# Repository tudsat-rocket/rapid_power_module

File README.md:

# Frodo Power Module

The battery boards for the FRoDO-rockets

## Version 1

@todo

## Version 2

The newest version of the battery developed for the FRoDO-M-rocket 

The battery module contains two lithium-ion cells in series, mounted on an *SRAD* *PCB* using a Keystone connector, allowing the replacement of battery cells. 

The battery features a linear charging IC supporting up to 700 mA of charge current and performs balancing of the cells, powered by the charge bus through a reverse current protection diode and a PTC fuse.

### Components

- 2x 3000 mA h Sony VTC6 18650 lithium-ion cells in series
- for other components see https://github.com/tudsat-rocket/frodo_power_module/blob/main/frodo_power_module.csv

### Usage

| Connector   | Purpose                                             |
| ----------- | --------------------------------------------------- |
| FC          | connect the flight computer. Outputs 8v with max ?a |
| SW          | Switch to turn the battery board on and off         |
| FC-CAN (2x) | CAN-bus for communication                           |
| BUS-A       |                                                     |
| BUS-B       |                                                     |

Spanning liegt von außen an, geht durch Arming Circuit,

## Version 3

tdb...

### ToDos for Hyacinth

- 3x 18650 lithium-ion cells in series

- New Charging IC due to more Cells

- Larger Board due to more Cells.

- Are 18650 a requirement or might they be exchanged against softbody batteries known from drones? (smaller PCB possible)

- Arming Schalter schaltet alles an.

- 

- 6 Pin durch 8 Pin ersetzen
  
  #### Possible new ICs

- https://www.ti.com/lit/ds/symlink/bq25820.pdf?ts=1739830650898&ref_url=https%253A%252F%252Fwww.ti.com%252Fbattery-management%252Fcharger-ics%252Fproducts.html

#### Ideas for Cell Voltage balancing

Good:
bq76PL536A: https://www.ti.com/lit/ds/symlink/bq76pl536a.pdf?ts=1740396899518&ref_url=https%253A%252F%252Fwww.ti.com%252Fproduct%252FBQ76PL536A - Does not require host, is availabel on lcsc: https://www.lcsc.com/search?q=BQ76PL536A&s_z=n_BQ76PL536A
BQ76922: https://www.ti.com/lit/ds/symlink/bq76922.pdf?ts=1740361016781

Okay:
BQ79606A-Q1: https://www.ti.com/lit/ds/symlink/bq79606a-q1.pdf?ts=1740391966301&ref_url=https%253A%252F%252Fwww.ti.com%252Fproduct%252FBQ79606A-Q1 - Availability is bad

Meh:
BQ76925: https://www.ti.com/lit/ds/symlink/bq76925.pdf?ts=1740385881236 - due to required host. This is just an analogue expander.

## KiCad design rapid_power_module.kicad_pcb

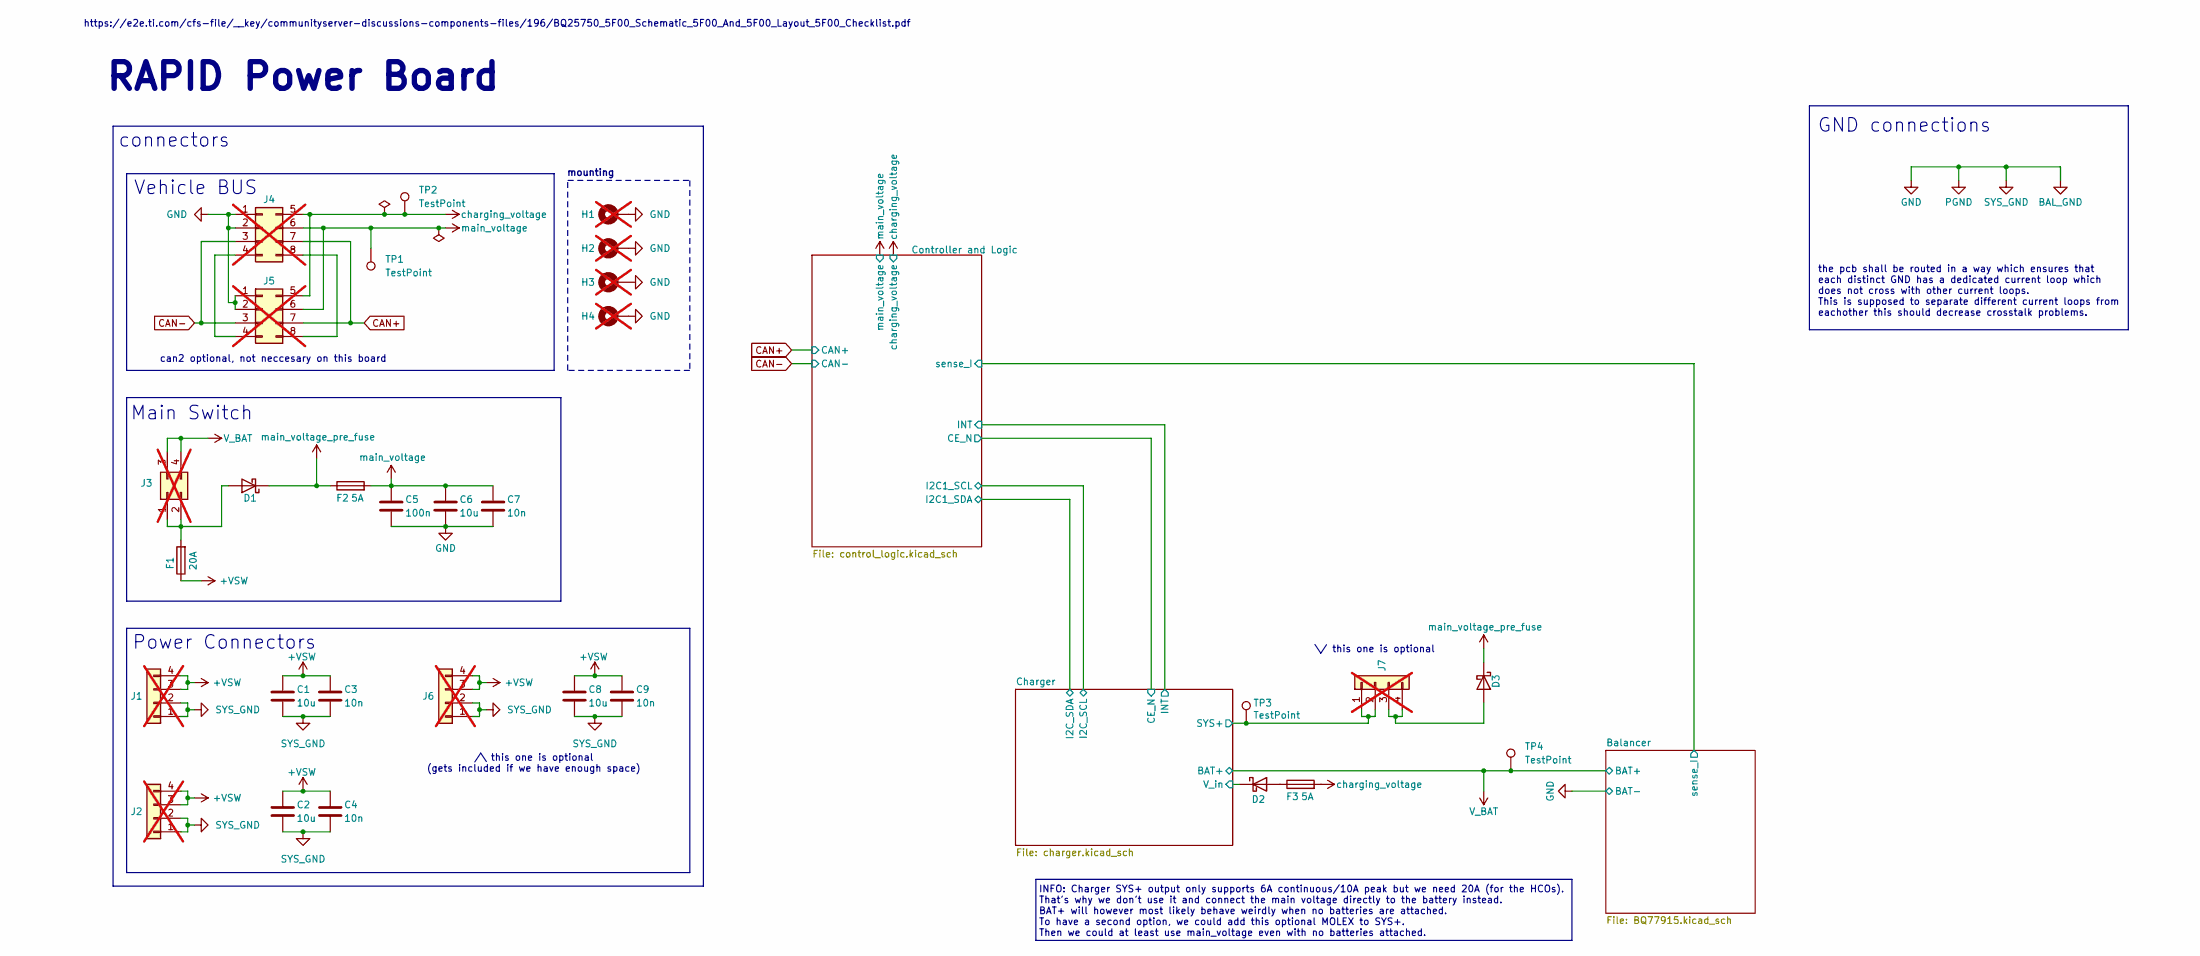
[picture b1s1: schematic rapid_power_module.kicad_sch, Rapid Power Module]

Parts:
C1, C2, C6, C8: 10u; C_0603_1608Metric; LCSC C96446
C3, C4, C7, C9: 10n; C_0402_1005Metric; LCSC C15195
C5: 100n; C_0402_1005Metric; LCSC C307331
D1, D2, D3: D_SMA; LCSC C22452
F1: 20A; Fuse_2010_5025Metric_Pad1.52x2.65mm_HandSolder; LCSC C2762483
F2, F3: 5A; Fuse_1206_3216Metric_Pad1.42x1.75mm_HandSolder; LCSC C48332
H1, H2, H3, H4: MountingHole_Pad; MountingHole_3.2mm_M3_Pad_Via; LCSC x; not fitted
J1, J2: Molex MicroFit 2x2; Molex_Micro-Fit_3.0_43045-0400_2x02_P3.00mm_Horizontal; Part# 0430450400; LCSC C122413; not fitted
J3: Molex MicroFit 2x2; Molex_Micro-Fit_3.0_43045-0400_2x02_P3.00mm_Horizontal; LCSC C122413; not fitted
J4, J5: Conn_02x04_Top_Bottom; Molex_Micro-Fit_3.0_43045-0800_2x04_P3.00mm_Horizontal; LCSC x; not fitted
J6, J7: Molex MicroFit 2x2; Molex_Micro-Fit_3.0_43045-0400_2x02_P3.00mm_Horizontal; Part# 0430450400; LCSC# C122413; not fitted
TP1, TP2, TP3, TP4: TestPoint; TestPoint_Pad_D2.0mm

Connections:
+VSW: C1.1, C2.1, C3.1, C4.1, C8.1, C9.1, F1.1, J1.3, J1.4, J2.3, J2.4, J6.3, J6.4
/Charger/SYS+: J7.1, J7.2, TP3.1 (1_1); also elsewhere on the board
/Charger/V_in: D2.1 (K); also elsewhere on the board
BAL_GND: C1.2, C2.2, C3.2, C4.2, C5.2, C6.2, C7.2, C8.2, C9.2, H1.1 (1_1), H2.1 (1_1), H3.1 (1_1), H4.1 (1_1), J1.1, J1.2, J2.1, J2.2, J4.1, J4.2, J5.1, J5.2, J6.1, J6.2; also elsewhere on the board
CAN+: J4.7, J5.7; also elsewhere on the board
CAN-: J4.3, J5.3; also elsewhere on the board
unnamed: D1.2 (A), F1.2, J3.1, J3.2
unnamed: D2.2 (A), F3.1
unnamed: D3.2 (A), J7.3, J7.4
unnamed: J4.4, J5.4
unnamed: J4.8, J5.8
V_BAT: J3.3, J3.4, TP4.1 (1_1); also elsewhere on the board
charging_voltage: F3.2, J4.5, J5.5, TP2.1 (1_1); also elsewhere on the board
main_voltage: C5.1, C6.1, C7.1, F2.2, J4.6, J5.6, TP1.1 (1_1); also elsewhere on the board
main_voltage_pre_fuse: D1.1 (K), D3.1 (K), F2.1

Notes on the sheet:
the pcb shall be routed in a way which ensures that each distinct GND has a dedicated current loop which does not cross with other current loops. This is supposed to separate different current loops from eachother this should decrease crosstalk problems.
connectors
can2 optional, not neccesary on this board
Vehicle BUS
Main Switch
RAPID Power Board
https://e2e.ti.com/cfs-file/__key/communityserver-discussions-components-files/196/BQ25750_5F00_Schematic_5F00_And_5F00_Layout_5F00_Checklist.pdf
\/ this one is optional
INFO: Charger SYS+ output only supports 6A continuous/10A peak but we need 20A (for the HCOs). That's why we don't use it and connect the main voltage directly to the battery instead. BAT+ will however most likely behave weirdly when no batteries are attached. To have a second option, we could add 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
mounting
/\ this one is optional (gets included if we have enough space)
Power Connectors
GND connections

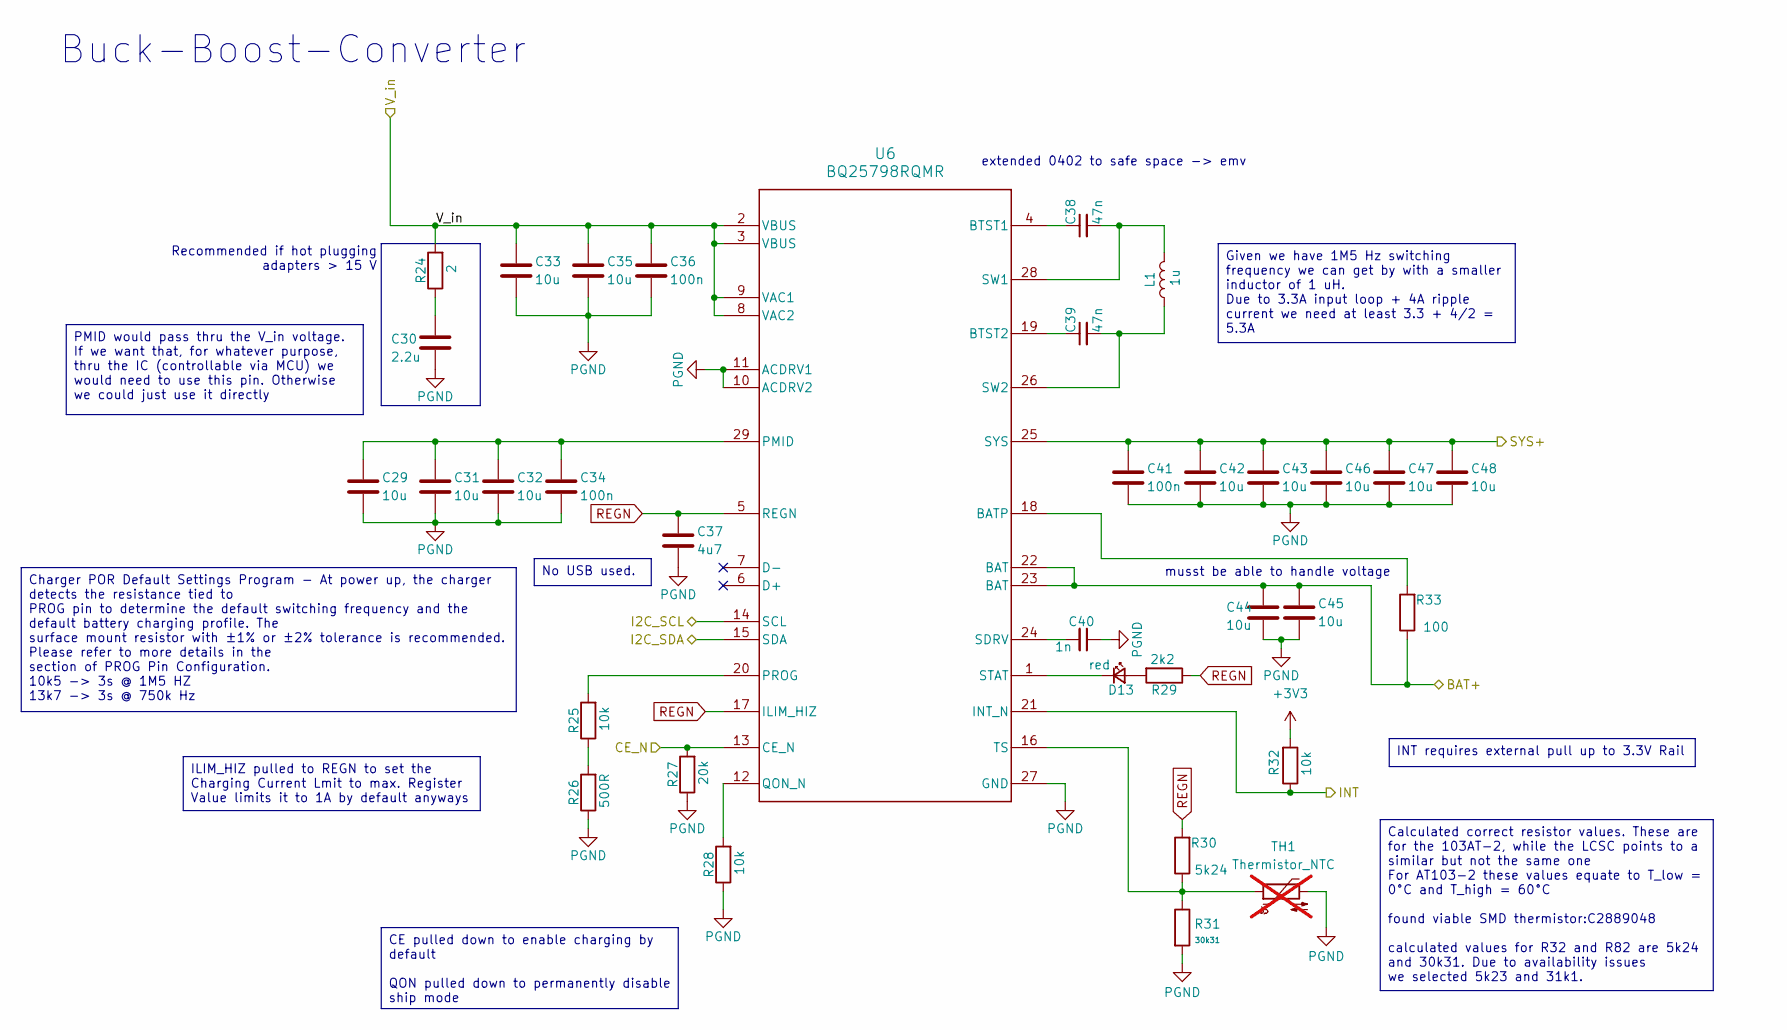
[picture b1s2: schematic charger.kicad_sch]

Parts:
C29, C31, C32, C33, C35, C42, C43, C44, C45, C46, C47, C48: 10u; C_0603_1608Metric; LCSC C96446
C30: 2.2u; C_0805_2012Metric; LCSC C377773
C34, C36, C41: 100n; C_0402_1005Metric; LCSC C307331
C37: 4u7; C_0402_1005Metric; LCSC C23733
C38, C39: 47n; C_0402_1005Metric; LCSC C82219
C40: 1n; C_0402_1005Metric; LCSC C1523
D13: red; LED_0603_1608Metric; LCSC C2286
L1: 1u; L_Wurth_WE-LQSH-3012; LCSC C7423316
R24: 2; R_0603_1608Metric; LCSC C22977
R25, R28, R32: 10k; R_0402_1005Metric; LCSC C25744
R26: 500R; R_0402_1005Metric; LCSC C25123
R27: 20k; R_0603_1608Metric; LCSC C4184
R29: 2k2; R_0402_1005Metric; LCSC C25879
R30: 5k24; R_0603_1608Metric; LCSC C23068
R31: 30k31; R_0805_2012Metric; LCSC C21841
R33: 100; R_0402_1005Metric; LCSC C25076
TH1: Thermistor_NTC; R_0603_1608Metric_Pad0.98x0.95mm_HandSolder; LCSC C2889048; not fitted
U6: BQ25798RQMR; IC_BQ25798RQMR; LCSC C2876593

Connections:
+3V3: R32.2; also elsewhere on the board
/Charger/CE_N: R27.2, U6.13 (CE_N); also elsewhere on the board
/Charger/INT: R32.1, U6.21 (INT_N); also elsewhere on the board
/Charger/SYS+: C41.1, C42.1, C43.1, C46.1, C47.1, C48.1, U6.25 (SYS); also elsewhere on the board
/Charger/V_in: C33.1, C35.1, C36.1, R24.2, U6.2 (VBUS), U6.3 (VBUS), U6.8 (VAC2), U6.9 (VAC1); also elsewhere on the board
BAL_GND: C29.2, C30.2, C31.2, C32.2, C33.2, C34.2, C35.2, C36.2, C37.2, C40.1, C41.2, C42.2, C43.2, C44.2, C45.2, C46.2, C47.2, C48.2, R26.1, R27.1, R28.1, R31.2, TH1.2, U6.10 (ACDRV2), U6.11 (ACDRV1), U6.27 (GND); also elsewhere on the board
I2C1_SCL: U6.14 (SCL); also elsewhere on the board
I2C1_SDA: U6.15 (SDA); also elsewhere on the board
unnamed: C30.1, R24.1
unnamed: D13.2 (A), R29.2
unnamed: D13.1 (K), U6.1 (STAT)
unnamed: R25.1, R26.2
unnamed: R33.2, U6.18 (BATP)
unnamed: C38.1, U6.4 (BTST1)
unnamed: C39.1, U6.19 (BTST2)
unnamed: C29.1, C31.1, C32.1, C34.1, U6.29 (PMID)
unnamed: R25.2, U6.20 (PROG)
unnamed: R28.2, U6.12 (QON_N)
unnamed: C40.2, U6.24 (SDRV)
unnamed: C38.2, L1.2, U6.28 (SW1)
unnamed: C39.2, L1.1, U6.26 (SW2)
unnamed: R30.1, R31.1, TH1.1, U6.16 (TS)
REGN: C37.1, R29.1, R30.2, U6.5 (REGN), U6.17 (ILIM_HIZ)
V_BAT: C44.1, C45.1, R33.1, U6.22 (BAT), U6.23 (BAT); also elsewhere on the board

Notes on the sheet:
extended 0402 to safe space -> emv
Buck-Boost-Converter
Recommended if hot plugging adapters > 15 V
musst be able to handle voltage
ILIM_HIZ pulled to REGN to set the Charging Current Lmit to max. Register Value limits it to 1A by default anyways
Given we have 1M5 Hz switching frequency we can get by with a smaller inductor of 1 uH. Due to 3.3A input loop + 4A ripple current we need at least 3.3 + 4/2 = 5.3A
INT requires external pull up to 3.3V Rail
Calculated correct resistor values. These are for the 103AT-2, while the LCSC points to a similar but not the same one For AT103-2 these values equate to T_low = 0°C and T_high = 60°C found viable SMD thermistor:C2889048 calculated values for R32 and R82 are 5k24 and 30k31. Due to availability issu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
PMID would pass thru the V_in voltage. If we want that, for whatever purpose, thru the IC (controllable via MCU) we would need to use this pin. Otherwise we could just use it directly
CE pulled down to enable charging by default QON pulled down to permanently disable ship mode
No USB used.
Charger POR Default Settings Program - At power up, the charger detects the resistance tied to PROG pin to determine the default switching frequency and the default battery charging profile. The surface mount resistor with ±1% or ±2% tolerance is recommended. Please refer to more details in the sec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

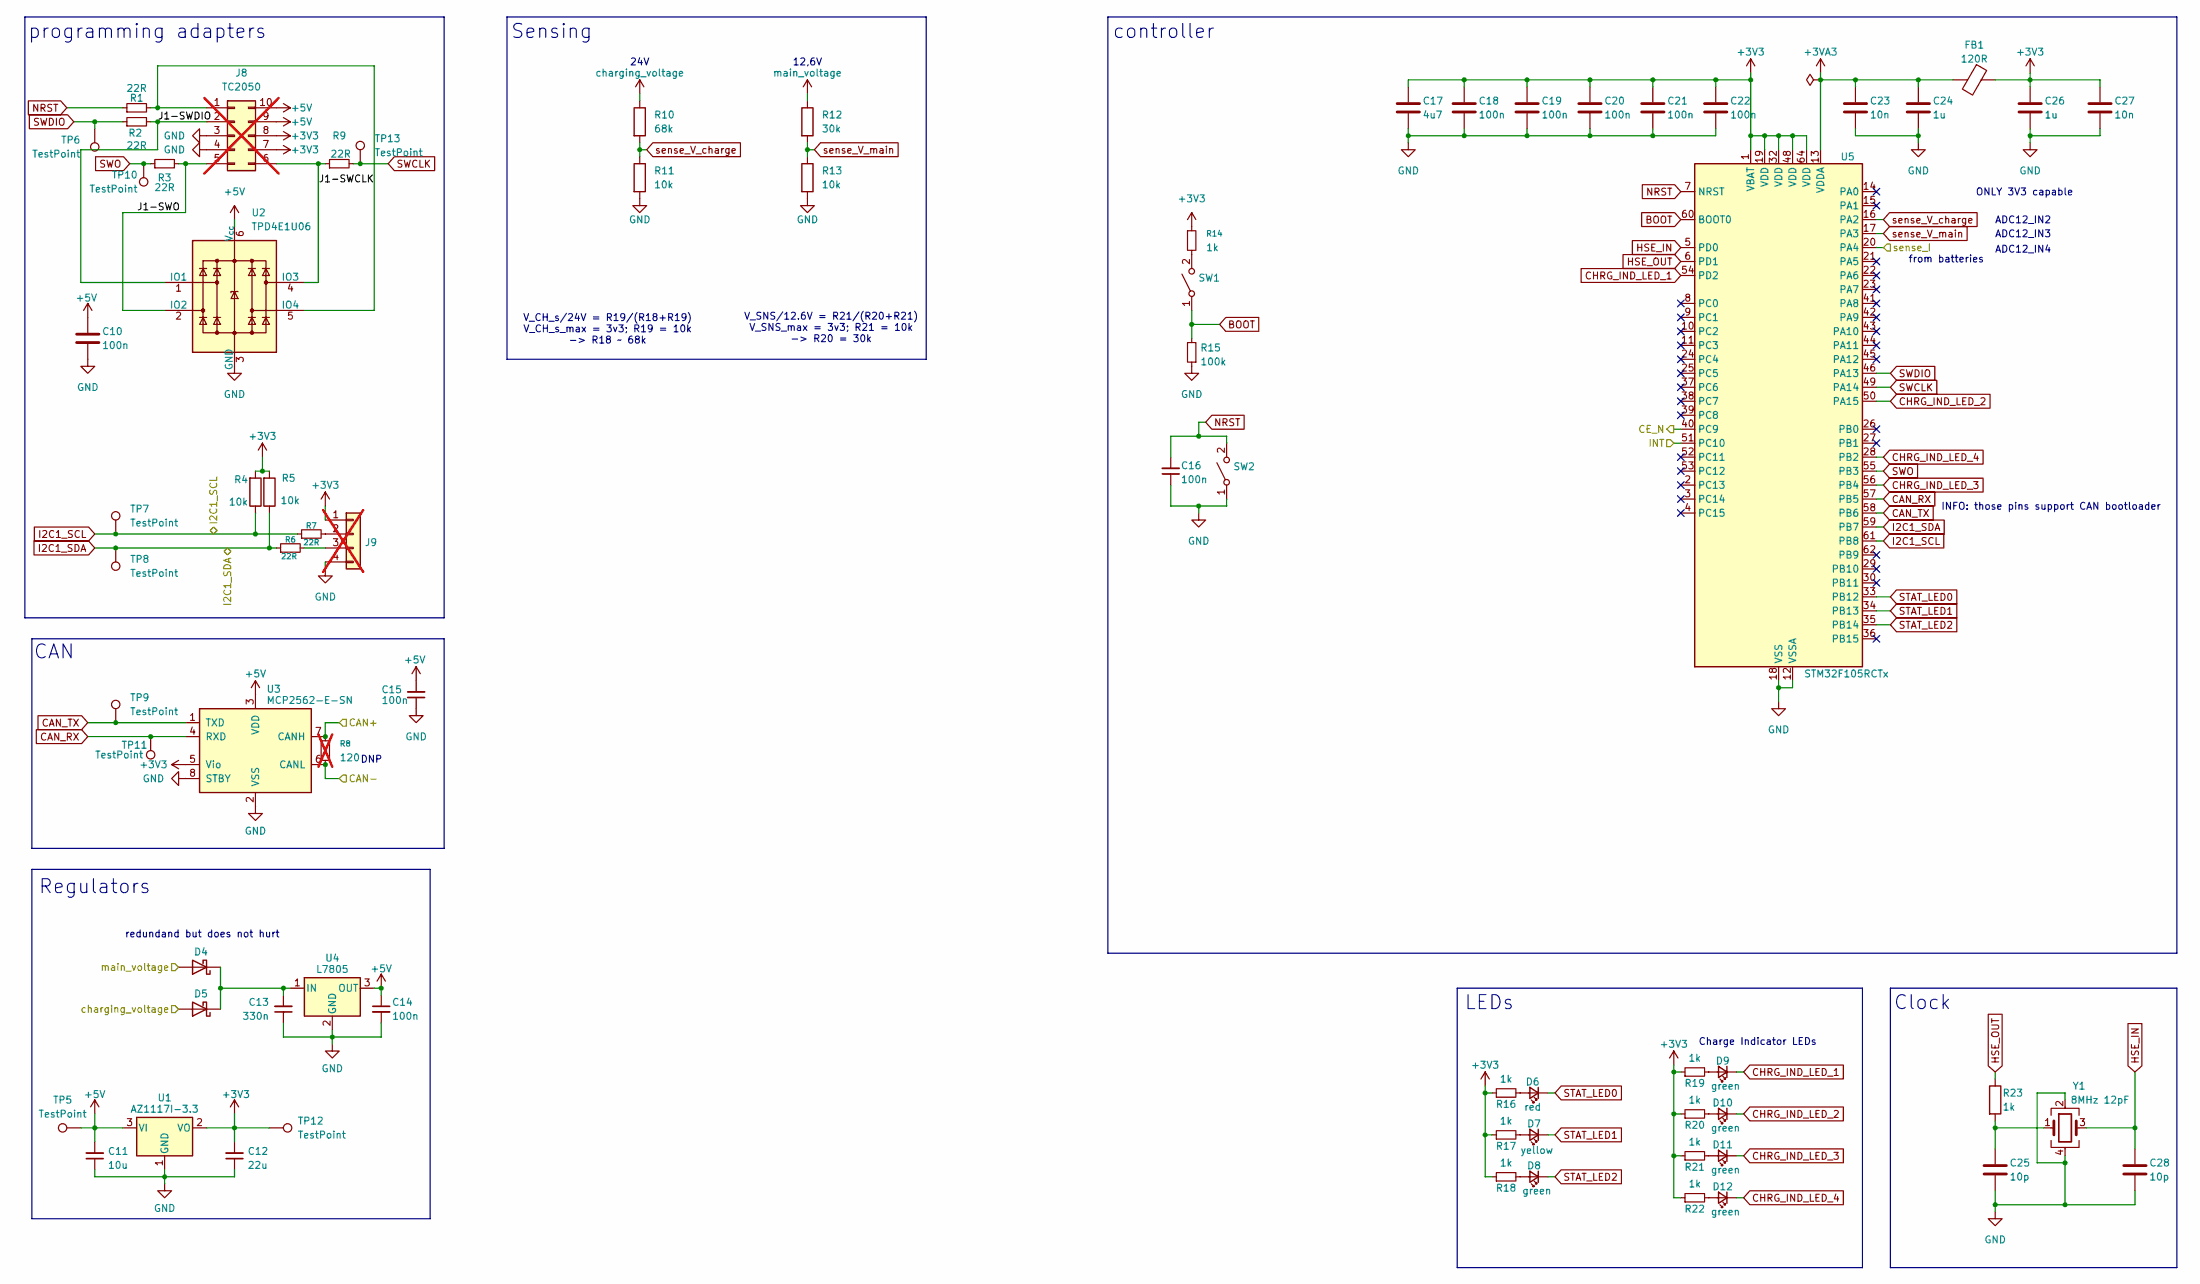
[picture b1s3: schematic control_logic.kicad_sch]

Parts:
C10, C15, C18, C19, C20, C21, C22: 100n; C_0402_1005Metric; LCSC C307331
C11: 10u; C_1206_3216Metric; Part# CL31A106KBHNNNE; LCSC C13585
C12: 22u; C_1206_3216Metric; Part# CL31A226KAHNNNE; LCSC C12891
C13: 330n; C_0603_1608Metric; Part# CL10B474KA8NNNC; LCSC C1615
C14: 100n; C_0402_1005Metric; Part# CC0603KRX7R9BB104; LCSC C307331
C16: 100n; C_0402_1005Metric; Part# CL10B104KB8NNNC; LCSC C307331
C17: 4u7; C_0402_1005Metric; LCSC C23733
C23, C27: 10n; C_0402_1005Metric; LCSC C15195
C24, C26: 1u; C_0402_1005Metric; LCSC C52923
C25, C28: 10p; C_0402_1005Metric; LCSC C32949
D4, D5: D_SMA; LCSC C22452
D6: red; LED_0603_1608Metric; LCSC C2286
D7: yellow; LED_0805_2012Metric; LCSC C2296
D8, D9, D10, D11, D12: green; LED_0805_2012Metric; LCSC C2297
FB1: 120R; L_0603_1608Metric; Part# BLM18PG121SN1D; LCSC C14709
J8: TC2050; Tag-Connect_TC2050-IDC-FP_2x05_P1.27mm_Vertical; LCSC x; not fitted
J9: SWD Header; PinHeader_1x04_P2.54mm_Vertical_SMD_Pin1Left; LCSC x; not fitted
R1, R2, R3, R9: 22R; R_0402_1005Metric; Part# RC0603FR-0710KL; LCSC C25092
R4, R5, R11, R13: 10k; R_0402_1005Metric; LCSC C25744
R6, R7: 22R; R_0402_1005Metric; Part# RC0603FR-0722RL; LCSC C25092
R8: 120; C_0402_1005Metric; LCSC C25079; not fitted
R10: 68k; R_0603_1608Metric; LCSC C23231
R12: 30k; R_0603_1608Metric; LCSC C22984
R14, R16, R17, R18, R19, R20, R21, R22, R23: 1k; R_0402_1005Metric; LCSC C11702
R15: 100k; R_0402_1005Metric; Part# RC0603FR-0710KL; LCSC C25741
SW1, SW2: SW_SPST_TS-1088-xR020; LCSC C720477
TP5, TP6, TP7, TP8, TP9, TP10, TP11, TP12, TP13: TestPoint; TestPoint_Pad_D2.0mm
U1: AZ1117I-3.3; SOT-223-3_TabPin2; Part# AZ1117CH-3.3TRG1; LCSC C92102
U2: TPD4E1U06; SOT-563; LCSC C527516
U3: MCP2562-E-SN; SOIC-8_3.9x4.9mm_P1.27mm; Part# MCP2562-H/SN; DigiKey# MCP2562-H/SN
U4: L7805; TO-252-2; Part# L78M05ABDT-TR; LCSC C58069
U5: STM32F105RCTx; LQFP-64_10x10mm_P0.5mm; LCSC C8345
Y1: 8MHz 12pF; Crystal_SMD_5032-4Pin_5.0x3.2mm; Part# 5TJ480000NYLBC; LCSC C2149245

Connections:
+3V3: C12.2, C17.1, C18.1, C19.1, C20.1, C21.1, C22.1, C26.1, C27.1, FB1.1, J8.7, J8.8, J9.1, R4.2, R5.2, R14.1, R16.1, R17.1, R18.1, R19.1, R20.1, R21.1, R22.1, TP12.1 (1_1), U1.2 (VO), U3.5 (Vio), U5.1 (VBAT), U5.19 (VDD), U5.32 (VDD), U5.48 (VDD), U5.64 (VDD); also elsewhere on the board
+3VA3: C23.1, C24.1, FB1.2, U5.13 (VDDA)
+5V: C10.1, C11.2, C14.1, C15.2, J8.9, J8.10, TP5.1 (1_1), U1.3 (VI), U2.6 (V_{cc}), U3.3 (VDD), U4.3 (OUT)
/Balancer/sense_I: U5.20 (PA4); also elsewhere on the board
/Charger/CE_N: U5.40 (PC9); also elsewhere on the board
/Charger/INT: U5.51 (PC10); also elsewhere on the board
/Controller and Logic/J1-SWCLK: J8.6, R9.1, U2.4 (IO3)
/Controller and Logic/J1-SWDIO: J8.2, R2.2, U2.1 (IO1)
/Controller and Logic/J1-SWO: J8.5, R3.2, U2.2 (IO2)
BAL_GND: C10.2, C11.1, C12.1, C13.1, C14.2, C15.1, C16.1, C17.2, C18.2, C19.2, C20.2, C21.2, C22.2, C23.2, C24.2, C25.2, C26.2, C27.2, C28.2, J8.3, J8.4, J9.4, R11.2, R13.2, R15.1, SW2.1 (A), U1.1 (GND), U2.3 (GND), U3.2 (VSS), U3.8 (STBY), U4.2 (GND), U5.12 (VSSA), U5.18 (VSS), U5.31 (VSS), U5.47 (VSS), U5.63 (VSS), Y1.2, Y1.4; also elsewhere on the board
BOOT: R15.2, SW1.1 (A), U5.60 (BOOT0)
CAN+: R8.1, U3.7 (CANH); also elsewhere on the board
CAN-: R8.2, U3.6 (CANL); also elsewhere on the board
CAN_RX: TP11.1 (1_1), U3.4 (RXD), U5.57 (PB5)
CAN_TX: TP9.1 (1_1), U3.1 (TXD), U5.58 (PB6)
CHRG_IND_LED_1: D9.1 (K), U5.54 (PD2)
CHRG_IND_LED_2: D10.1 (K), U5.50 (PA15)
CHRG_IND_LED_3: D11.1 (K), U5.56 (PB4)
CHRG_IND_LED_4: D12.1 (K), U5.28 (PB2)
HSE_IN: C28.1, U5.5 (PD0), Y1.3
HSE_OUT: R23.1, U5.6 (PD1)
I2C1_SCL: R4.1, R7.1, TP7.1 (1_1), U5.61 (PB8); also elsewhere on the board
I2C1_SDA: R5.1, R6.1, TP8.1 (1_1), U5.59 (PB7); also elsewhere on the board
NRST: C16.2, R1.1, SW2.2 (B), U5.7 (NRST)
unnamed: C25.1, R23.2, Y1.1
unnamed: C13.2, D4.1 (K), D5.1 (K), U4.1 (IN)
unnamed: D6.2 (A), R16.2
unnamed: D7.2 (A), R17.2
unnamed: D8.2 (A), R18.2
unnamed: D9.2 (A), R19.2
unnamed: D10.2 (A), R20.2
unnamed: D11.2 (A), R21.2
unnamed: D12.2 (A), R22.2
unnamed: J8.1, R1.2, U2.5 (IO4)
unnamed: J9.2, R7.2
unnamed: J9.3, R6.2
unnamed: R14.2, SW1.2 (B)
STAT_LED0: D6.1 (K), U5.33 (PB12)
STAT_LED1: D7.1 (K), U5.34 (PB13)
STAT_LED2: D8.1 (K), U5.35 (PB14)
SWCLK: R9.2, TP13.1 (1_1), U5.49 (PA14)
SWDIO: R2.1, TP6.1 (1_1), U5.46 (PA13)
SWO: R3.1, TP10.1 (1_1), U5.55 (PB3)
charging_voltage: D5.2 (A), R10.1; also elsewhere on the board
main_voltage: D4.2 (A), R12.1; also elsewhere on the board
sense_V_charge: R10.2, R11.1, U5.16 (PA2)
sense_V_main: R12.2, R13.1, U5.17 (PA3)

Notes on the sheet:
Clock
INFO: those pins support CAN bootloader
controller
from batteries
Sensing
Charge Indicator LEDs
Regulators
redundand but does not hurt
V_SNS/12.6V = R21/(R20+R21) V_SNS_max = 3v3; R21 = 10k -> R20 = 30k
LEDs
ADC12_IN3
ADC12_IN4
programming adapters
ONLY 3V3 capable
12,6V
ADC12_IN2
DNP
CAN
24V
V_CH_s/24V = R19/(R18+R19) V_CH_s_max = 3v3; R19 = 10k -> R18 ~ 68k

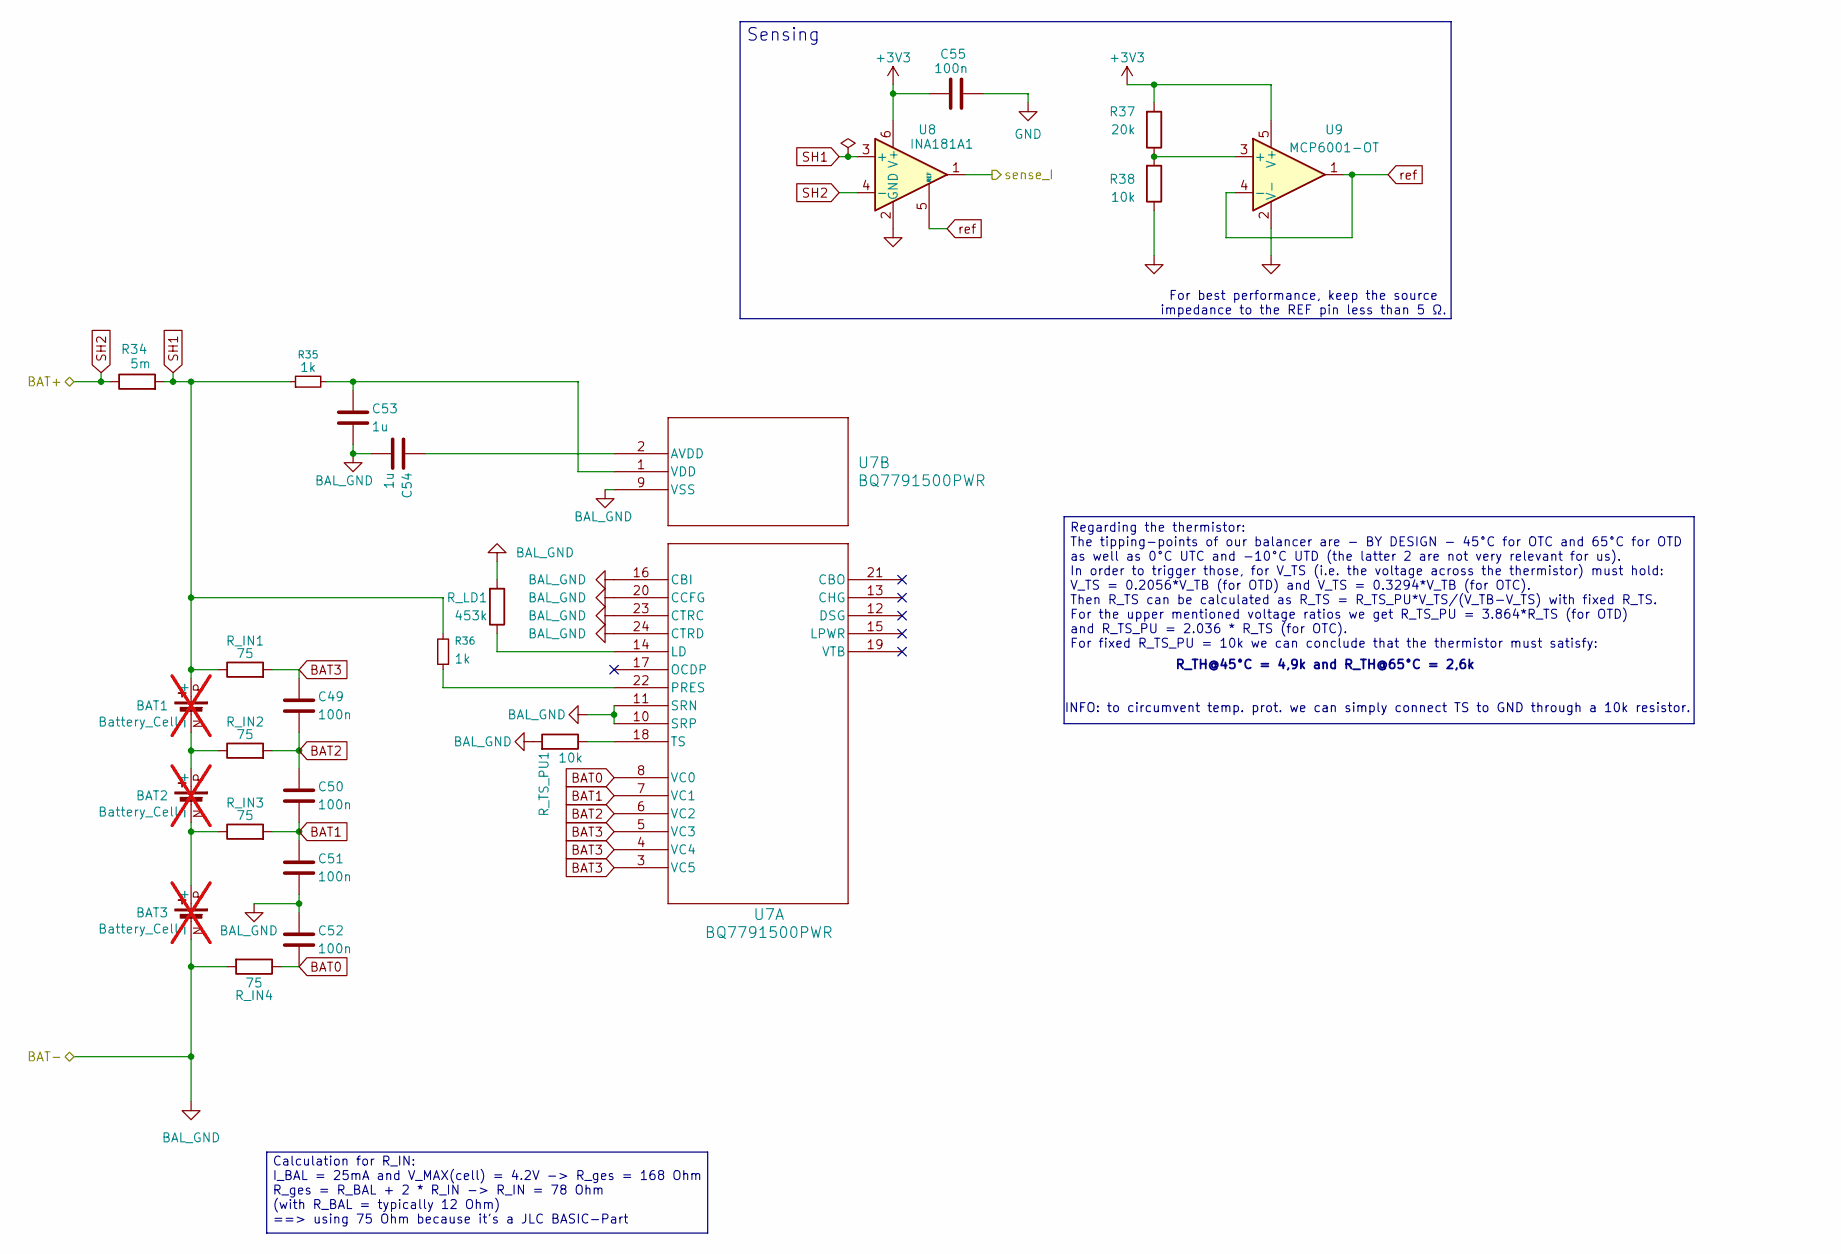
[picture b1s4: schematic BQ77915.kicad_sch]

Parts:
BAT1, BAT2, BAT3: Battery_Cell; BAT_1043; LCSC x; not fitted
C49, C50, C51, C52: 100n; C_0402_1005Metric; LCSC C307331
C53, C54: 1u; C_0402_1005Metric; LCSC C52923
C55: 100n; C_0402_1005Metric; LCSC C1525
R34: 5m; R_2512_6332Metric_Pad1.40x3.35mm_HandSolder; Part# DSLR-K-3-5F; LCSC C41382686
R35, R36: 1k; R_0402_1005Metric; LCSC C11702
R37: 20k; R_0402_1005Metric_Pad0.72x0.64mm_HandSolder; LCSC C25765
R38: 10k; R_0402_1005Metric_Pad0.72x0.64mm_HandSolder; LCSC C25744
R_IN1, R_IN2, R_IN3, R_IN4: 75; R_0603_1608Metric; LCSC C4275
R_LD1: 453k; R_0402_1005Metric; LCSC C27009
R_TS_PU1: 10k; R_0402_1005Metric; LCSC C25744
U7: BQ7791500PWR; TSSOP-24_4.4x7.8mm_P0.65mm; LCSC C2876946
U8: INA181A1; SOT-23-6; LCSC C2058943
U9: MCP6001-OT; SOT-23-5; LCSC C116490

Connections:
+3V3: C55.1, R37.2, U8.6 (V+), U9.5 (V+); also elsewhere on the board
/Balancer/sense_I: U8.1; also elsewhere on the board
BAL_GND: BAT3.N (-), C51.2, C52.1, C53.2, C54.2, C55.2, R38.1, R_IN4.2, R_LD1.2, R_TS_PU1.2, U7.9 (VSS), U7.10 (SRP), U7.11 (SRN), U7.16 (CBI), U7.20 (CCFG), U7.23 (CTRC), U7.24 (CTRD), U8.2 (GND), U9.2 (V-); also elsewhere on the board
BAT0: C52.2, R_IN4.1, U7.8 (VC0)
BAT1: C50.2, C51.1, R_IN3.2, U7.7 (VC1)
BAT2: C49.2, C50.1, R_IN2.2, U7.6 (VC2)
BAT3: C49.1, R_IN1.2, U7.3 (VC5), U7.4 (VC4), U7.5 (VC3)
unnamed: BAT1.N (-), BAT2.P (+), R_IN2.1
unnamed: BAT2.N (-), BAT3.P (+), R_IN3.1
unnamed: R_LD1.1, U7.14 (LD)
unnamed: R36.1, U7.22 (PRES)
unnamed: R_TS_PU1.1, U7.18 (TS)
unnamed: C54.1, U7.2 (AVDD)
unnamed: C53.1, R35.2, U7.1 (VDD)
unnamed: R37.1, R38.2, U9.3 (+)
SH1: BAT1.P (+), R34.2, R35.1, R36.2, R_IN1.1, U8.3 (+)
V_BAT: R34.1, U8.4 (-); also elsewhere on the board
ref: U8.5 (REF), U9.1, U9.4 (-)

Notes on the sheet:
For best performance, keep the source impedance to the REF pin less than 5 Ω.
R_TH@45°C = 4,9k and R_TH@65°C = 2,6k
INFO: to circumvent temp. prot. we can simply connect TS to GND through a 10k resistor.
Calculation for R_IN: I_BAL = 25mA and V_MAX(cell) = 4.2V -> R_ges = 168 Ohm R_ges = R_BAL + 2 * R_IN -> R_IN = 78 Ohm (with R_BAL = typically 12 Ohm) ==> using 75 Ohm because it's a JLC BASIC-Part
Regarding the thermistor: The tipping-points of our balancer are - BY DESIGN - 45°C for OTC and 65°C for OTD as well as 0°C UTC and -10°C UTD (the latter 2 are not very relevant for us). In order to trigger those, for V_TS (i.e. the voltage across the thermistor) must hold: V_TS = 0.2056*V_TB (for 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
Sensing

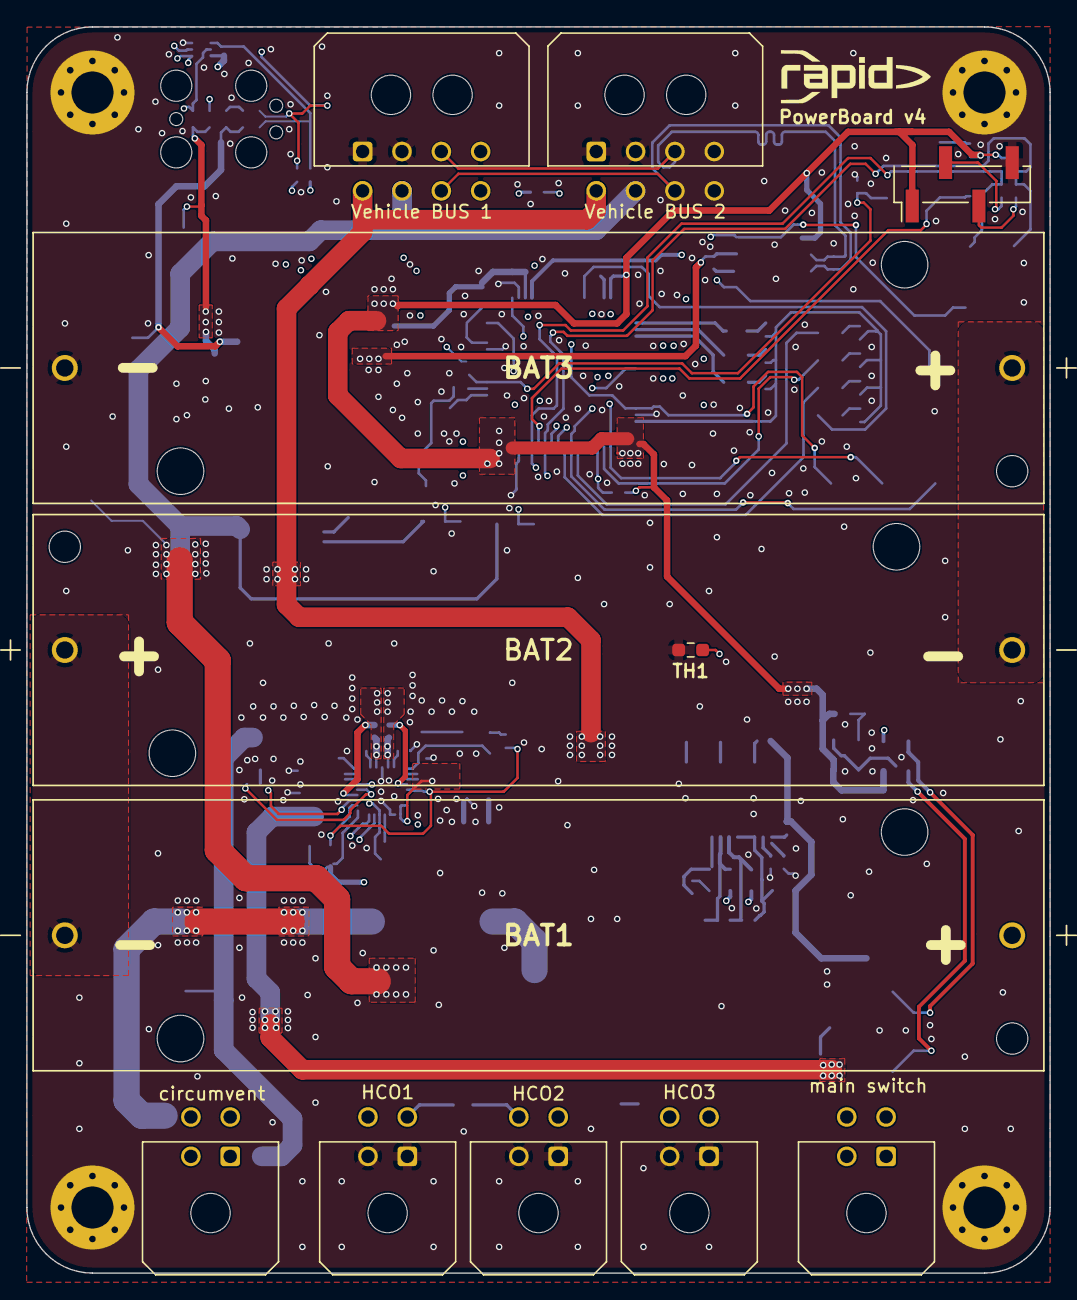
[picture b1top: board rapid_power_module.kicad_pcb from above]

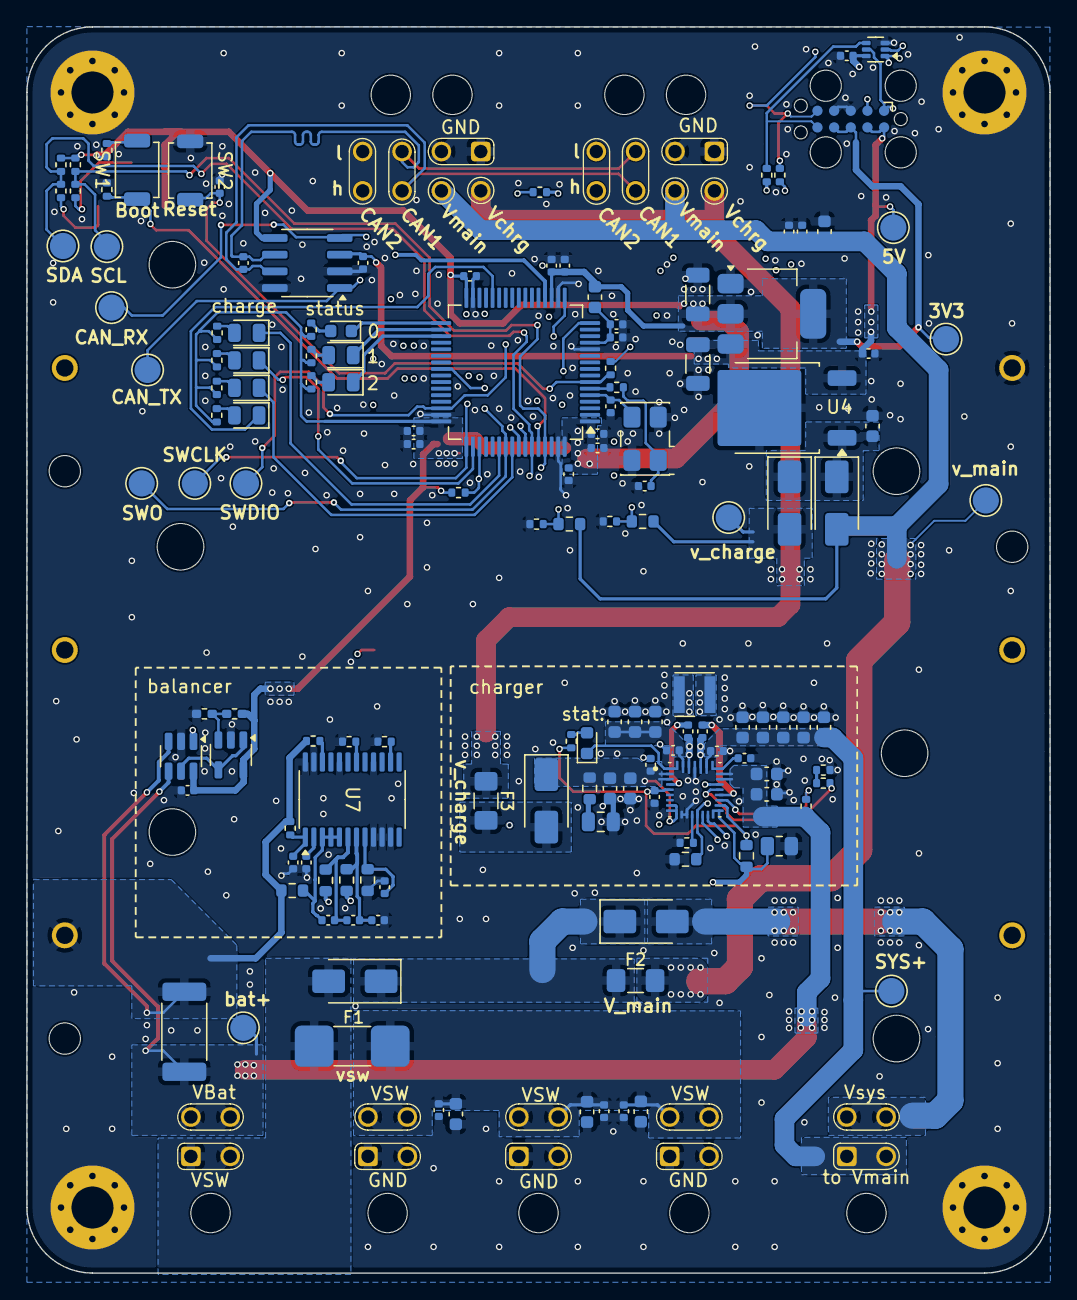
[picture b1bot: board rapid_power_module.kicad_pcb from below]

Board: 4 copper layers, 78.0 x 95.0 mm, 159 parts (143 on the bottom side), 86 nets.

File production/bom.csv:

Designator,Footprint,Quantity,Value,LCSC Part #
"C1, C2, C29, C31, C32, C33, C35, C42, C43, C44, C45, C46, C47, C48, C6, C8",0603,16,10u,C96446
"C10, C14, C15, C16, C18, C19, C20, C21, C22, C34, C36, C41, C49, C5, C50, C51, C52",0402,17,100n,C307331
C11,1206,1,10u,C13585
C12,1206,1,22u,C12891
C13,0603,1,330n,C1615
"C17, C37",0402,2,4u7,C23733
"C23, C27, C3, C4, C7, C9",0402,6,10n,C15195
"C24, C26, C53, C54",0402,4,1u,C52923
"C25, C28",0402,2,10p,C32949
C30,0805,1,2.2u,C377773
"C38, C39",0402,2,47n,C82219
C40,0402,1,1n,C1523
C55,0402,1,100n,C1525 
"D1, D2, D3, D4, D5",D_SMA,5,~,C22452
"D10, D11, D12, D8, D9",0805,5,green,C2297
"D13, D6",0603,2,red,C2286
D7,0805,1,yellow,C2296
F1,2010,1,20A,C2762483 
"F2, F3",1206,2,5A,C48332
FB1,0603,1,120R,C14709
L1,L_Wurth_WE-LQSH-3012,1,1u,C7423316
"R1, R2, R3, R6, R7, R9",0402,6,22R,C25092
R10,0603,1,68k,C23231
"R11, R13, R32, R38, R4, R5, R_TS_PU1",0402,7,10k,C25744
R12,0603,1,30k,C22984
"R14, R16, R17, R18, R19, R20, R21, R22, R23, R35, R36",0402,11,1k,C11702
R15,0402,1,100k,C25741
R24,0603,1,2,C22977 
"R25, R28",0402,2,10k,C25744 
R26,0402,1,500R, C25123 
R27,0603,1,20k,C4184
R29,0402,1,2k2,C25879
R30,0603,1,5k24,C23068
R31,0805,1,30k31,C21841
R33,0402,1,100,C25076
R34,2512,1,5m,C41382686
R37,0402,1,20k,C25765
"R_IN1, R_IN2, R_IN3, R_IN4",0603,4,75,C4275
R_LD1,0402,1,453k,C27009
"SW1, SW2",SW_SPST_TS-1088-xR020,2,~,C720477
"TP1, TP10, TP11, TP12, TP13, TP2, TP3, TP4, TP5, TP6, TP7, TP8, TP9",TestPoint_Pad_D2.0mm,13,TestPoint,
U1,SOT-223-3_TabPin2,1,AZ1117I-3.3,C92102
U2,SOT-563,1,TPD4E1U06,C527516
U3,SOIC-8_3.9x4.9mm_P1.27mm,1,MCP2562-E-SN,C191417
U4,TO-252-2,1,L7805,C58069
U5,LQFP-64_10x10mm_P0.5mm,1,STM32F105RCTx,C8345
U6,IC_BQ25798RQMR,1,BQ25798RQMR,C2876593
U7,TSSOP-24_4.4x7.8mm_P0.65mm,1,BQ7791500PWR,C2876946
U8,SOT-23-6,1,INA181A1,C2058943
U9,SOT-23-5,1,MCP6001-OT,C116490
Y1,Crystal_SMD_5032-4Pin_5.0x3.2mm,1,8MHz 12pF,C2149245
